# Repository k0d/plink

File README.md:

# Plink Debug Board
I need to write a description for this!

## Schematic

## MCU Pinout

## PCB

## 3D View

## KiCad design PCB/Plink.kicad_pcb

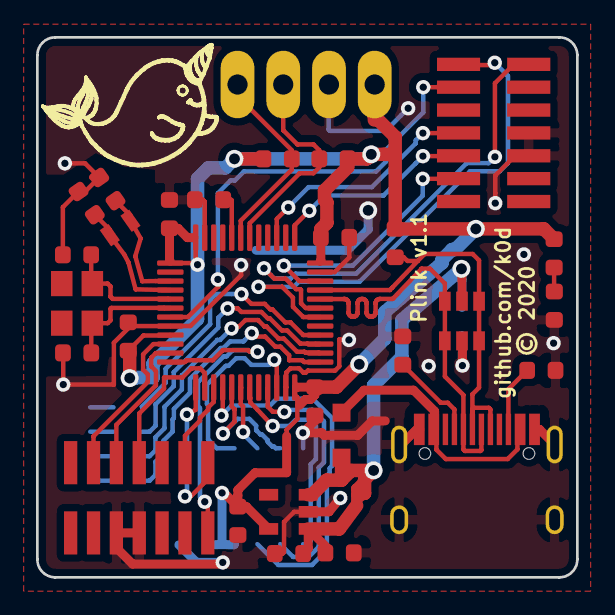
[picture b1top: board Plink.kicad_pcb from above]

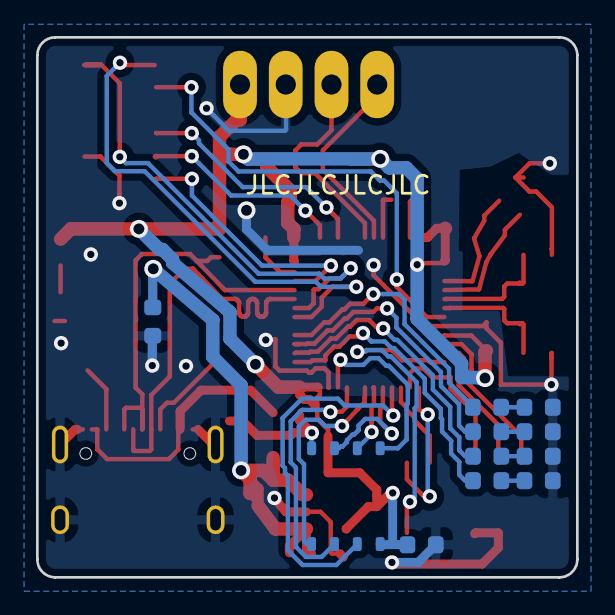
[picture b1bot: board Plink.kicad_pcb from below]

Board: 2 copper layers, 30.0 x 30.0 mm, 41 parts (12 on the bottom side), 42 nets.

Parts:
C1, C2: 10pF; C_0603
C3, C4, C9, C10, C11, C12, C13: 100nF; C_0603
C5, C8: 1uF; C_0603
C6, C7: 3.9pF; C_0603
D1: BAT60A; D_SOD_323
D2, D4: GREEN; LED_0603
D3: RED; LED_0603
D5: BLUE; LED_0603
D6: YELLOW; LED_0603
IC1: TLV75533PDBV; SOT-23-5
J1: USB_C_Socket_USB2.0; USB_C_Socket-C319148
J2: I2C_OLED; OLED_i2c
J3: STDC14; M_2x07_1.27_V_SMD
J4: Target STDC14; M_2x07_1.27_V_SMD
R1: 100k; R_0603
R2, R11: 5k1; R_0603
R3, R4: 4.7k; R_0603
R5: 1k5; R_0603
R6, R7, R8, R9, R10: 330; R_0603
U1: W25Q128JVPIM TR; WSON_8_6x5_1.27
U2: USBLC6-2SC6; SOT-23-6
U3: STM32L433CCT6; LQFP_48_7x7_0.5
X1: Narwahl
X2: 8MHz 8pF; Crystal_4p_3225
X3: 32.768KHz 12.5pF; Crystal_2p_2012

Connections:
+3V3: C4.2, C8.1, C10.2, C11.2, C12.2, C13.2, IC1.5, J2.1, R3.2, R4.2, R5.1, R6.1, U1.8, U3.1, U3.9, U3.24, U3.36, U3.48
+5V: C3.2, C5.2, C9.1, D1.1, IC1.1, IC1.3, U2.5
/BOOT0: R1.1, U3.44
/FLASH_CLK: U1.6, U3.21
/FLASH_CS: U1.1, U3.22
/FLASH_D0: U1.5, U3.19
/FLASH_D1: U1.2, U3.18
/FLASH_D2: U1.3, U3.17
/FLASH_D3: U1.7, U3.16
/I2C1_SCL: J2.3, R3.1, U3.42
/I2C1_SDA: J2.4, R4.1, U3.43
/NRST: J3.12, U3.7
/OSC32_IN: C6.1, U3.3, X3.2
/OSC32_OUT: C7.1, U3.4, X3.1
/OSC_IN: C1.1, U3.5, X2.2
/OSC_OUT: C2.1, U3.6, X2.1
/SWCLK: J3.6, U3.37
/SWDIO: J3.4, U3.34
/SWO: J3.8, U3.39
/T_NRST: J4.12, U3.15
/T_SWCLK: J4.6, U3.11
/T_SWDIO: J4.4, U3.10
/T_SWO: J4.8, U3.14
/T_VCP_RX: J4.13, U3.12
/T_VCP_TX: J4.14, U3.13
/USB+: J1.A6, J1.B6, R5.2, U2.3, U2.4, U3.33
/USB-: J1.A7, J1.B7, U2.1, U2.6, U3.32
/VCP_RX: J3.13, U3.31
/VCP_TX: J3.14, U3.30
GND: C1.2, C2.2, C3.1, C4.1, C5.1, C6.2, C7.2, C8.2, C9.2, C10.1, C11.1, C12.1, C13.1, D2.1, D3.1, D4.1, D5.1, D6.1, IC1.2, J1.A1, J1.A12, J1.B1, J1.B12, J1.S1, J2.2, J3.5, J3.7, J4.5, J4.7, R1.2, R2.1, R11.1, U1.4, U2.2, U3.8, U3.23, U3.35, U3.47
unnamed: D1.2, J1.A4, J1.A9, J1.B4, J1.B9
unnamed: D2.2, R6.2
unnamed: D3.2, R7.2
unnamed: D4.2, R8.2
unnamed: D5.2, R9.2
unnamed: D6.2, R10.2
unnamed: J1.A5, R2.2
unnamed: J1.B5, R11.2
unnamed: R7.1, U3.25
unnamed: R8.1, U3.26
unnamed: R9.1, U3.27
unnamed: R10.1, U3.28

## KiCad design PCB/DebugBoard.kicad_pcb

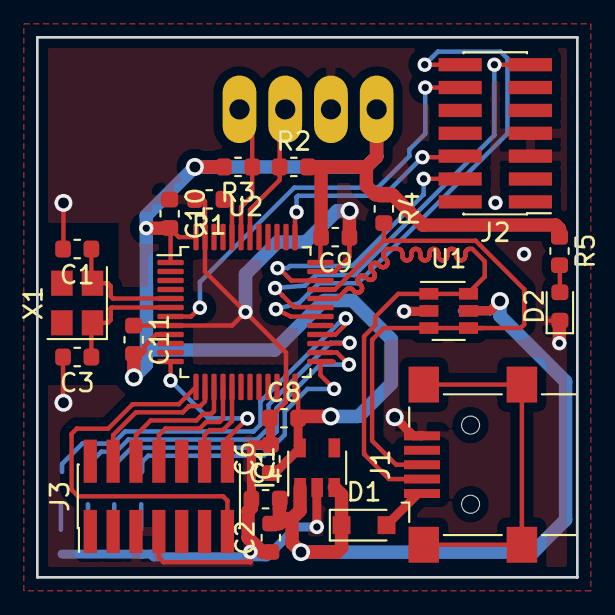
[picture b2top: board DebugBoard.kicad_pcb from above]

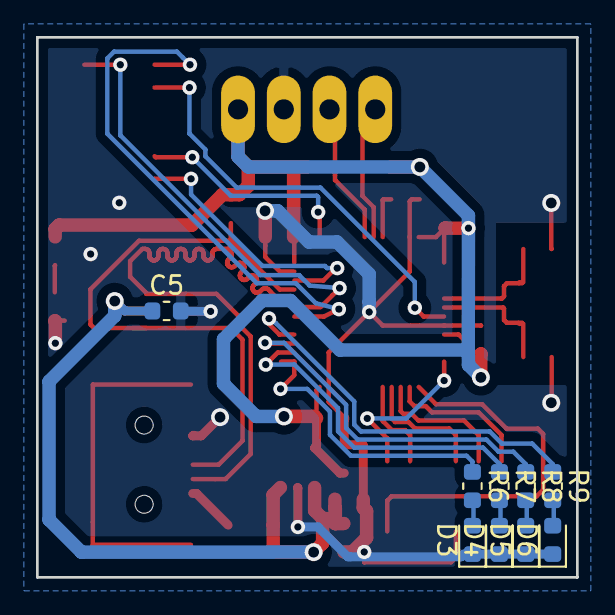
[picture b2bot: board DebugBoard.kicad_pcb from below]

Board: 2 copper layers, 30.0 x 30.0 mm, 33 parts (10 on the bottom side), 31 nets.

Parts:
C1, C3: 10pF; C_0603_1608Metric
C2, C5, C8, C9, C10, C11: 100nF; C_0603_1608Metric
C4, C6: 1uF; C_0603_1608Metric
D1: BAT60A; D_SOD-323_HandSoldering
D2, D4: GREEN; LED_0603_1608Metric
D3: RED; LED_0603_1608Metric
D5: BLUE; LED_0603_1608Metric
D6: YELLOW; LED_0603_1608Metric
IC1: TLV75533PDBV; SOT-23-5
J1: USB_B_Mini; USB_Mini-B_Lumberg_2486_01_Horizontal
J2: STDC14; PinHeader_2x07_P1.27mm_Vertical_SMD
J3: Target STDC14; PinHeader_2x07_P1.27mm_Vertical_SMD
J4: I2C_OLED; OLED_i2c
R1: 100k; R_0603_1608Metric
R2, R3: 4.7k; R_0603_1608Metric
R4: 1k5; R_0603_1608Metric
R5, R6, R7, R8, R9: 330; R_0603_1608Metric
U1: USBLC6-2SC6; SOT-23-6
U2: STM32F070CBTx; LQFP-48_7x7mm_P0.5mm
X1: NX3225GD; Crystal_SMD_3225-4Pin_3.2x2.5mm

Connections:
+3V3: C6.1, C8.2, C9.2, C10.2, C11.2, IC1.5, J4.1, R2.2, R3.2, R4.1, R5.1, U2.1, U2.9, U2.24, U2.36, U2.48
+5V: C2.2, C4.2, C5.1, D1.1, IC1.1, IC1.3, U1.5
/BOOT0: R1.1, U2.44
/DBG_CLK: J2.6, U2.37
/DBG_DIO: J2.4, U2.34
/I2C1_SCL: J4.3, R2.1, U2.42
/I2C1_SDA: J4.4, R3.1, U2.43
/NRST: J2.12, U2.7
/OSC_IN: C1.1, U2.5, X1.2
/OSC_OUT: C3.1, U2.6, X1.1
/T_DBG_CLK: J3.6, U2.15
/T_DBG_DIO: J3.4, U2.14
/T_DBG_SWO: J3.8, U2.16
/T_NRST: J3.12, U2.17
/T_VCP_RX: J3.13, U2.13
/T_VCP_TX: J3.14, U2.12
/USB+: J1.3, R4.2, U1.3, U1.4, U2.33
/USB-: J1.2, U1.1, U1.6, U2.32
/VCP_RX: J2.13, U2.31
/VCP_TX: J2.14, U2.30
GND: C1.2, C2.1, C3.2, C4.1, C5.2, C6.2, C8.1, C9.1, C10.1, C11.1, D2.1, D3.1, D4.1, D5.1, D6.1, IC1.2, J1.5, J2.5, J2.7, J3.5, J3.7, J4.2, R1.2, U1.2, U2.8, U2.23, U2.35, U2.47
unnamed: D1.2, J1.1
unnamed: D2.2, R5.2
unnamed: D3.2, R6.2
unnamed: D4.2, R7.2
unnamed: D5.2, R8.2
unnamed: D6.2, R9.2
unnamed: R6.1, U2.25
unnamed: R7.1, U2.26
unnamed: R8.1, U2.27
unnamed: R9.1, U2.28

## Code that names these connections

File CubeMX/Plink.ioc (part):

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Mcu.Name=STM32L433C(B-C)Tx
Mcu.Package=LQFP48
Mcu.UserName=STM32L433CCTx
PA0.GPIOParameters=GPIO_Label
PA0.GPIO_Label=T_SWO
PA0.Signal=GPIO_Output
PA1.GPIOParameters=GPIO_Label
PA1.GPIO_Label=T_NRST
PA1.Signal=GPIO_Output
PA10.GPIOParameters=GPIO_Label
PA10.GPIO_Label=VCP_RX
PA10.Mode=Asynchronous
PA10.Signal=USART1_RX
PA11.GPIOParameters=GPIO_Label
PA11.GPIO_Label=USB-
PA11.Mode=Device
PA11.Signal=USB_DM
PA12.GPIOParameters=GPIO_Label
PA12.GPIO_Label=USB+
PA12.Mode=Device
PA12.Signal=USB_DP
PA13\ (JTMS-SWDIO).GPIOParameters=GPIO_Label
PA13\ (JTMS-SWDIO).GPIO_Label=SWDIO
PA13\ (JTMS-SWDIO).Mode=Trace_Asynchronous_SW
PA13\ (JTMS-SWDIO).Signal=SYS_JTMS-SWDIO
PA14\ (JTCK-SWCLK).GPIOParameters=GPIO_Label
PA14\ (JTCK-SWCLK).GPIO_Label=SWCLK
PA14\ (JTCK-SWCLK).Mode=Trace_Asynchronous_SW
PA14\ (JTCK-SWCLK).Signal=SYS_JTCK-SWCLK
PA2.GPIOParameters=GPIO_Label
PA2.GPIO_Label=T_VCP_TX
PA2.Mode=Asynchronous
PA2.Signal=USART2_TX
PA3.GPIOParameters=GPIO_Label
PA3.GPIO_Label=T_VCP_RX
PA3.Mode=Asynchronous
PA3.Signal=USART2_RX
PA4.GPIOParameters=GPIO_Label
PA4.GPIO_Label=T_SWDIO
PA4.Signal=GPIO_Output
PA5.GPIOParameters=GPIO_Label
PA5.GPIO_Label=T_SWCLK
PA5.Signal=GPIO_Output
PA6.GPIOParameters=GPIO_Label
PA6.GPIO_Label=FLASH_D3
PA6.Mode=Single Bank 1
PA6.Signal=QUADSPI_BK1_IO3
PA7.GPIOParameters=GPIO_Label
PA7.GPIO_Label=FLASH_D2
PA7.Mode=Single Bank 1
PA7.Signal=QUADSPI_BK1_IO2
PA9.GPIOParameters=GPIO_Label
PA9.GPIO_Label=VCP_TX
PA9.Mode=Asynchronous
PA9.Signal=USART1_TX
PB0.GPIOParameters=GPIO_Label
PB0.GPIO_Label=FLASH_D1
PB0.Mode=Single Bank 1
PB0.Signal=QUADSPI_BK1_IO1
PB1.GPIOParameters=GPIO_Label
PB1.GPIO_Label=FLASH_D0
PB1.Mode=Single Bank 1
PB1.Signal=QUADSPI_BK1_IO0
PB10.GPIOParameters=GPIO_Label
PB10.GPIO_Label=FLASH_CLK
PB10.Mode=Single Bank 1
PB10.Signal=QUADSPI_CLK
PB11.GPIOParameters=GPIO_Label
PB11.GPIO_Label=FLASH_CS
PB11.Mode=Single Bank 1
PB11.Signal=QUADSPI_BK1_NCS
PB12.GPIOParameters=GPIO_Label
PB12.GPIO_Label=LED_RED
PB12.Signal=GPIO_Output
PB13.GPIOParameters=GPIO_Label
PB13.GPIO_Label=LED_GREEN
PB13.Signal=GPIO_Output
PB14.GPIOParameters=GPIO_Label
PB14.GPIO_Label=LED_BLUE
PB14.Signal=GPIO_Output
PB15.GPIOParameters=GPIO_Label
PB15.GPIO_Label=LED_YELLOW
PB15.Signal=GPIO_Output
PB3\ (JTDO-TRACESWO).GPIOParameters=GPIO_Label
PB3\ (JTDO-TRACESWO).GPIO_Label=SWO
PB3\ (JTDO-TRACESWO).Mode=Trace_Asynchronous_SW
PB3\ (JTDO-TRACESWO).Signal=SYS_JTDO-SWO
PB6.Mode=I2C
PB6.Signal=I2C1_SCL
PB7.Mode=I2C
PB7.Signal=I2C1_SDA
PC14-OSC32_IN\ (PC14).GPIOParameters=GPIO_Label
PC14-OSC32_IN\ (PC14).GPIO_Label=OSC32_IN
PC14-OSC32_IN\ (PC14).Mode=LSE-External-Oscillator
PC14-OSC32_IN\ (PC14).Signal=RCC_OSC32_IN
PC15-OSC32_OUT\ (PC15).GPIOParameters=GPIO_Label
PC15-OSC32_OUT\ (PC15).GPIO_Label=OSC32_OUT
PC15-OSC32_OUT\ (PC15).Mode=LSE-External-Oscillator
PC15-OSC32_OUT\ (PC15).Signal=RCC_OSC32_OUT
PH0-OSC_IN\ (PH0).GPIOParameters=GPIO_Label
PH0-OSC_IN\ (PH0).GPIO_Label=OSC_IN
PH0-OSC_IN\ (PH0).Mode=HSE-External-Oscillator
PH0-OSC_IN\ (PH0).Signal=RCC_OSC_IN
PH1-OSC_OUT\ (PH1).GPIOParameters=GPIO_Label
PH1-OSC_OUT\ (PH1).GPIO_Label=OSC_OUT
PH1-OSC_OUT\ (PH1).Mode=HSE-External-Oscillator
PH1-OSC_OUT\ (PH1).Signal=RCC_OSC_OUT
RCC.HSE_VALUE=8000000
RCC.SYSCLKFreq_VALUE=80000000
RCC.SYSCLKSource=RCC_SYSCLKSOURCE_PLLCLK
board=custom

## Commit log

2020-05-19 Moved USB, fixed traces, updated silkscreen
2020-05-19 Adds checklist, uart rx/tx solder bridges
2020-06-06 v1.1
2020-06-07 Updates to the footprints

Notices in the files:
PCB/Plink.kicad_pcb:
© 2020
